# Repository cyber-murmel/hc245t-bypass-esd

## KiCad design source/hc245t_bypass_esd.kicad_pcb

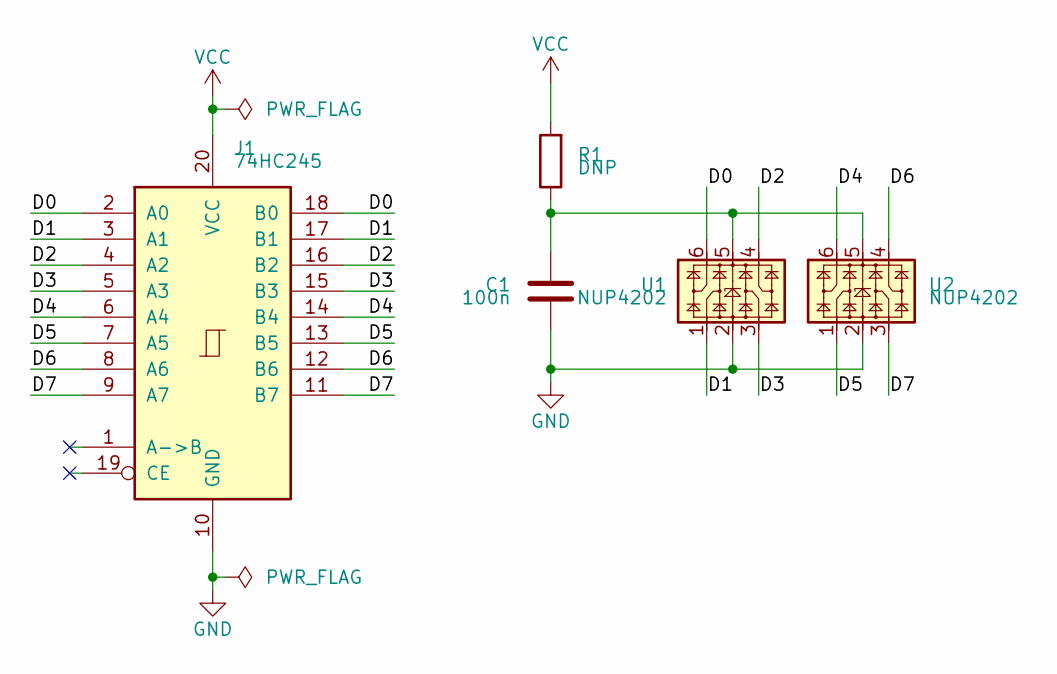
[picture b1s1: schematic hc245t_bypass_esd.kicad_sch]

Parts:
C1: 100n; C_0402_1005Metric
J1: 74HC245; TSSOP-20_4.4x6.5mm_P0.65mm
R1: DNP; R_0402_1005Metric
U1, U2: NUP4202; SOT-363_SC-70-6

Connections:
/D0: J1.2 (A0), J1.18 (B0), U1.6
/D1: J1.3 (A1), J1.17 (B1), U1.1
/D2: J1.4 (A2), J1.16 (B2), U1.4
/D3: J1.5 (A3), J1.15 (B3), U1.3
/D4: J1.6 (A4), J1.14 (B4), U2.6
/D5: J1.7 (A5), J1.13 (B5), U2.1
/D6: J1.8 (A6), J1.12 (B6), U2.4
/D7: J1.9 (A7), J1.11 (B7), U2.3
GND: C1.2, J1.10 (GND), U1.2, U2.2
unnamed: C1.1, R1.1, U1.5, U2.5
VCC: J1.20 (VCC), R1.2

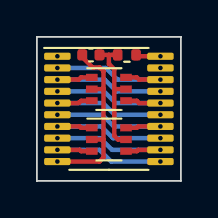
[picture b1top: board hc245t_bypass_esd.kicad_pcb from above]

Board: 2 copper layers, 8.0 x 8.0 mm, 5 parts (0 on the bottom side), 11 nets.

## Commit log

2022-01-10 initial design
2022-01-10 added renderings
2022-01-11 made pannel 5x3 instead of 6x6
